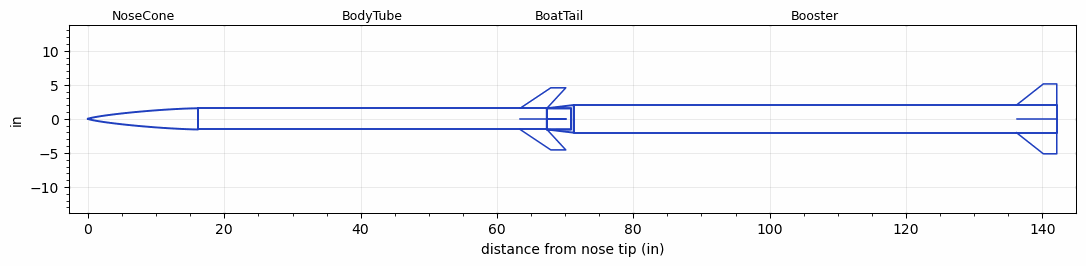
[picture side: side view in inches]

<RASAeroDocument>
 <FileVersion>2</FileVersion>
 <RocketDesign>
  <NoseCone>
   <Length>16.142</Length>
   <Diameter>3.11</Diameter>
   <Shape>Von Karman Ogive</Shape>
   <Location>0</Location>
  </NoseCone>
  <BodyTube>
   <Length>51.182</Length>
   <Diameter>3.11</Diameter>
   <Location>16.142</Location>
   <BoattailLength>3.543</BoattailLength>
   <BoattailRearDiameter>3.1</BoattailRearDiameter>
   <Fin>
    <Count>4</Count>
    <Chord>3.93</Chord>
    <Span>3</Span>
    <SweepDistance>4.5</SweepDistance>
    <TipChord>2.2</TipChord>
    <Thickness>0.118</Thickness>
    <LERadius>0.01</LERadius>
    <Location>3.93</Location>
    <AirfoilSection>Hexagonal</AirfoilSection>
    <FX1>1</FX1>
    <FX3>1</FX3>
   </Fin>
  </BodyTube>
  <BoatTail>
   <Length>3.543</Length>
   <Diameter>3.11</Diameter>
   <RearDiameter>3.1</RearDiameter>
   <Location>67.324</Location>
  </BoatTail>
  <Booster>
   <Length>70.866</Length>
   <Diameter>4.055</Diameter>
   <InsideDiameter>3.11</InsideDiameter>
   <Location>67.324</Location>
   <ShoulderLength>3.937</ShoulderLength>
   <Fin>
    <Count>4</Count>
    <Chord>5.906</Chord>
    <Span>3.1</Span>
    <SweepDistance>3.94</SweepDistance>
    <TipChord>1.969</TipChord>
    <Thickness>0.118</Thickness>
    <LERadius>0.01</LERadius>
    <Location>5.906</Location>
    <AirfoilSection>Hexagonal</AirfoilSection>
    <FX1>1</FX1>
    <FX3>1</FX3>
   </Fin>
  </Booster>
  <Surface>Smooth Paint</Surface>
  <ModifiedBarrowman>False</ModifiedBarrowman>
  <Turbulence>True</Turbulence>
  <UseBooster1>False</UseBooster1>
  <UseBooster2>False</UseBooster2>
 </RocketDesign>
 <LaunchSite>
  <Altitude>0</Altitude>
  <Pressure>0</Pressure>
  <RodAngle>0</RodAngle>
  <RodLength>16</RodLength>
  <Temperature>74</Temperature>
  <WindSpeed>0</WindSpeed>
 </LaunchSite>
 <Recovery>
  <Altitude1>1000</Altitude1>
  <Altitude2>1700</Altitude2>
  <DeviceType1>Parachute</DeviceType1>
  <DeviceType2>Parachute</DeviceType2>
  <Event1>False</Event1>
  <Event2>False</Event2>
  <Size1>1</Size1>
  <Size2>1</Size2>
  <EventType1>Apogee</EventType1>
  <EventType2>Altitude</EventType2>
  <CD1>1.33</CD1>
  <CD2>1.33</CD2>
 </Recovery>
 <SimulationList>
  <Simulation>
   <SustainerEngine>M2045-BS  (CTI)</SustainerEngine>
   <SustainerLaunchWt>19.3</SustainerLaunchWt>
   <SustainerNozzleDiameter>1.23</SustainerNozzleDiameter>
   <SustainerCG>44.48</SustainerCG>
   <SustainerIgnitionDelay>15</SustainerIgnitionDelay>
   <Booster1Engine>N1560-WH-MB-P  (CTI)</Booster1Engine>
   <Booster1LaunchWt>64.3</Booster1LaunchWt>
   <Booster1SeparationDelay>0</Booster1SeparationDelay>
   <Booster1IgnitionDelay>0</Booster1IgnitionDelay>
   <Booster1CG>89.63</Booster1CG>
   <Booster1NozzleDiameter>1.75</Booster1NozzleDiameter>
   <IncludeBooster1>True</IncludeBooster1>
   <Booster2Delay>0</Booster2Delay>
   <IncludeBooster2>False</IncludeBooster2>
   <TimetoApogee>113.5037</TimetoApogee>
   <MaxAltitude>155494.2</MaxAltitude>
   <MaxVelocity>3815.352</MaxVelocity>
  </Simulation>
  <Simulation>
   <SustainerEngine>M2045-BS  (CTI)</SustainerEngine>
   <SustainerLaunchWt>44.48</SustainerLaunchWt>
   <SustainerNozzleDiameter>1.23</SustainerNozzleDiameter>
   <SustainerCG>19.3</SustainerCG>
   <SustainerIgnitionDelay>15</SustainerIgnitionDelay>
   <Booster1Engine>O3400-IM-P  (CTI)</Booster1Engine>
   <Booster1LaunchWt>66.5</Booster1LaunchWt>
   <Booster1SeparationDelay>0</Booster1SeparationDelay>
   <Booster1IgnitionDelay>0</Booster1IgnitionDelay>
   <Booster1CG>90.43</Booster1CG>
   <Booster1NozzleDiameter>1.75</Booster1NozzleDiameter>
   <IncludeBooster1>True</IncludeBooster1>
   <Booster2Delay>0</Booster2Delay>
   <IncludeBooster2>False</IncludeBooster2>
   <TimetoApogee>92.91013</TimetoApogee>
   <MaxAltitude>116196</MaxAltitude>
   <MaxVelocity>2406.852</MaxVelocity>
  </Simulation>
 </SimulationList>
</RASAeroDocument>
